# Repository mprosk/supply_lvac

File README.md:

# Low Voltage AC Modular Supply
12V AC input rectified to +12VDC and -12VDC across 8 standard Eurorack-style IDC connectors

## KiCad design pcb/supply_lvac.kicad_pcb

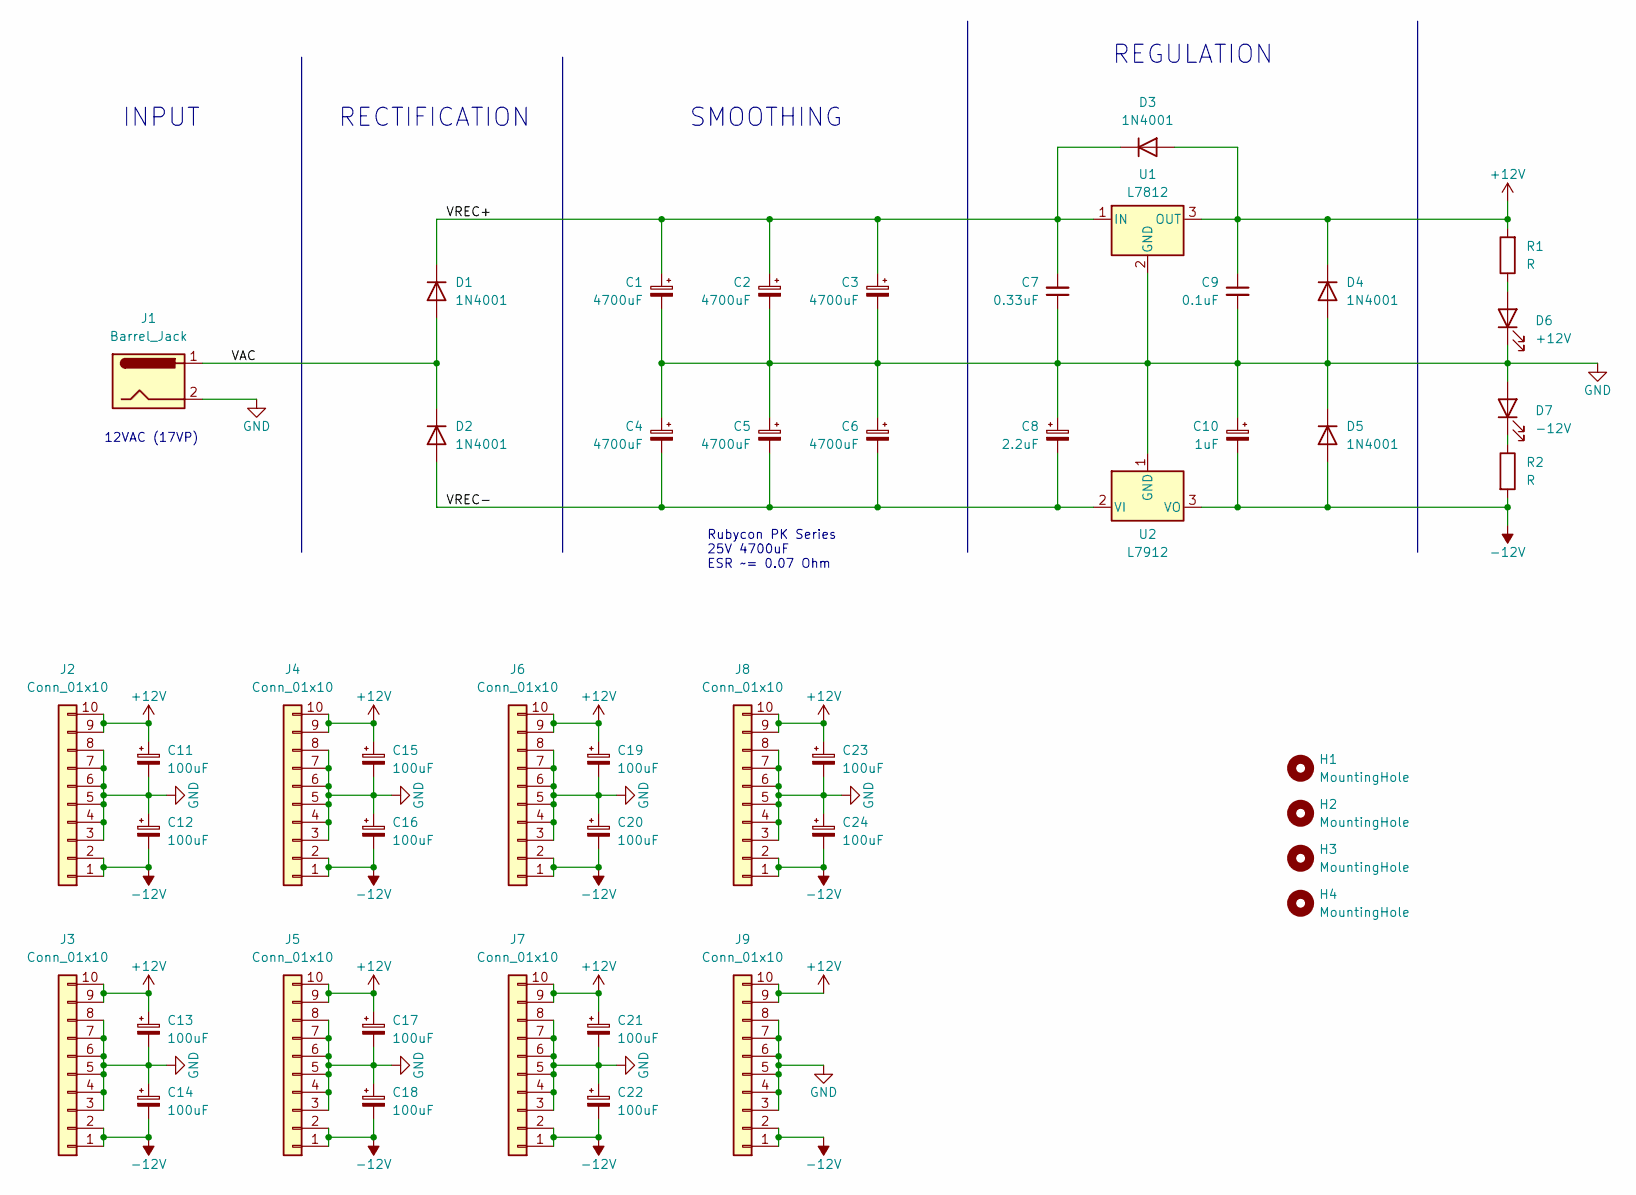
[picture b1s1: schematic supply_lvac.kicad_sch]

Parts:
C1, C2, C3, C4, C5, C6: 4700uF; CP_Radial_D16.0mm_P7.50mm
C7: 0.33uF; C_Disc_D3.0mm_W1.6mm_P2.50mm
C8: 2.2uF; CP_Radial_D4.0mm_P2.00mm
C9: 0.1uF; C_Disc_D3.0mm_W1.6mm_P2.50mm
C10: 1uF; CP_Radial_D4.0mm_P1.50mm
C11, C12, C13, C14, C15, C16, C17, C18, C19, C20, C21, C22, C23, C24: 100uF; CP_Radial_D4.0mm_P2.00mm
D1, D2, D3, D4, D5: 1N4001; D_DO-41_SOD81_P10.16mm_Horizontal
D6: +12V; LED_D5.0mm
D7: -12V; LED_D5.0mm
H1, H2, H3, H4: MountingHole; MountingHole_3.2mm_M3
J1: Barrel_Jack; Molex_KK-254_AE-6410-02A_1x02_P2.54mm_Vertical
J2, J3, J4, J5, J6, J7, J8, J9: Conn_01x10; IDC-Header_2x05_P2.54mm_Vertical
R1, R2: R; R_Axial_DIN0207_L6.3mm_D2.5mm_P2.54mm_Vertical
U1: L7812; TO-220-3_Vertical
U2: L7912; TO-220-3_Vertical

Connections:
+12V: C9.1, C11.1, C13.1, C15.1, C17.1, C19.1, C21.1, C23.1, D3.2 (A), D4.1 (K), J2.9, J2.10, J3.9, J3.10, J4.9, J4.10, J5.9, J5.10, J6.9, J6.10, J7.9, J7.10, J8.9, J8.10, J9.9, J9.10, R1.2, U1.3 (OUT)
-12V: C10.2, C12.2, C14.2, C16.2, C18.2, C20.2, C22.2, C24.2, D5.2 (A), J2.1, J2.2, J3.1, J3.2, J4.1, J4.2, J5.1, J5.2, J6.1, J6.2, J7.1, J7.2, J8.1, J8.2, J9.1, J9.2, R2.2, U2.3 (VO)
/VAC: D1.2 (A), D2.1 (K), J1.1
/VREC+: C1.1, C2.1, C3.1, C7.2, D1.1 (K), D3.1 (K), U1.1 (IN)
/VREC-: C4.2, C5.2, C6.2, C8.2, D2.2 (A), U2.2 (VI)
GND: C1.2, C2.2, C3.2, C4.1, C5.1, C6.1, C7.1, C8.1, C9.2, C10.1, C11.2, C12.1, C13.2, C14.1, C15.2, C16.1, C17.2, C18.1, C19.2, C20.1, C21.2, C22.1, C23.2, C24.1, D4.2 (A), D5.1 (K), D6.1 (K), D7.2 (A), J1.2, J2.3, J2.4, J2.5, J2.6, J2.7, J2.8, J3.3, J3.4, J3.5, J3.6, J3.7, J3.8, J4.3, J4.4, J4.5, J4.6, J4.7, J4.8, J5.3, J5.4, J5.5, J5.6, J5.7, J5.8, J6.3, J6.4, J6.5, J6.6, J6.7, J6.8, J7.3, J7.4, J7.5, J7.6, J7.7, J7.8, J8.3, J8.4, J8.5, J8.6, J8.7, J8.8, J9.3, J9.4, J9.5, J9.6, J9.7, J9.8, U1.2 (GND), U2.1 (GND)
unnamed: D6.2 (A), R1.1
unnamed: D7.1 (K), R2.1

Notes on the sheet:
INPUT
SMOOTHING
12VAC (17VP)
REGULATION
RECTIFICATION
Rubycon PK Series 25V 4700uF ESR ~= 0.07 Ohm

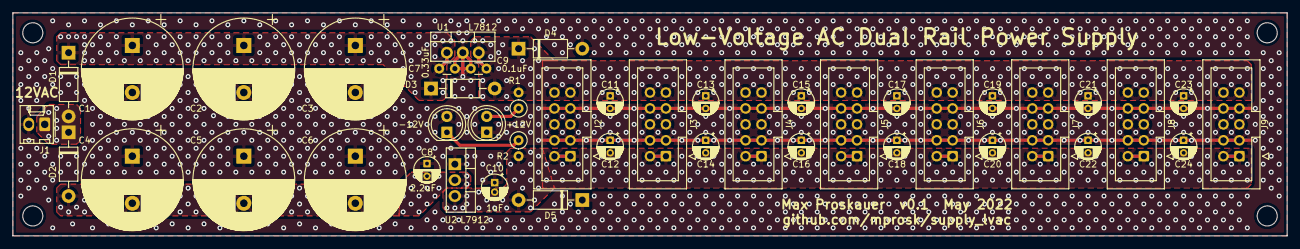
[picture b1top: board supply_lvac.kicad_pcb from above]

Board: 2 copper layers, 203.2 x 35.6 mm, 48 parts (0 on the bottom side), 8 nets.

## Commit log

2022-05-18 Start layout
2022-05-21 Start via stitching
2022-05-22 Complete layout. Export gerbers
